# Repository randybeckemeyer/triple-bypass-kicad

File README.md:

# Triple Bypass
The Triple Bypass is an audio/video mod board designed for Sega Genesis/Megadrive consoles. It contains bypass circuitry for RGBs video and also contains a Mega Amp 2.0 audio amplifier designed by Ace and Villahed94.

http://www.sega-16.com/forum/showthread.php?31989-Take-your-Genesis-audio-to-the-next-level-The-Mega-Amp-2-0-is-here!

The schematic circuits are the same as db-electronics version 0.3. The schematic and layout are redrawn with as many built-in library parts as possible. The schematic is shuffled around but contains equivelant circuits with jumpers added. The board is larger than db-electronics version 0.3 and is untested.

# Install Instructions
Use the Mega Amp 2.0 thread for wire tap points on various console revisions.

# Uses Solder Jumpers instead of different Bill of Materials
This is intended to be built with a pick and place assemble line. No need for resistor kits or boards with different build options. The board is designed to be fully populated with one BOM. There are solder jumpers for attenuation resistors and to choose which sound chip your system contains.
* YM2612
* ASIC YM3438
* GOAC YM3438

# PCB Finish
There are no special requirements for the finish of this PCB - a 1.6mm PCB with HASL finish is perfectly acceptable for this PCB.

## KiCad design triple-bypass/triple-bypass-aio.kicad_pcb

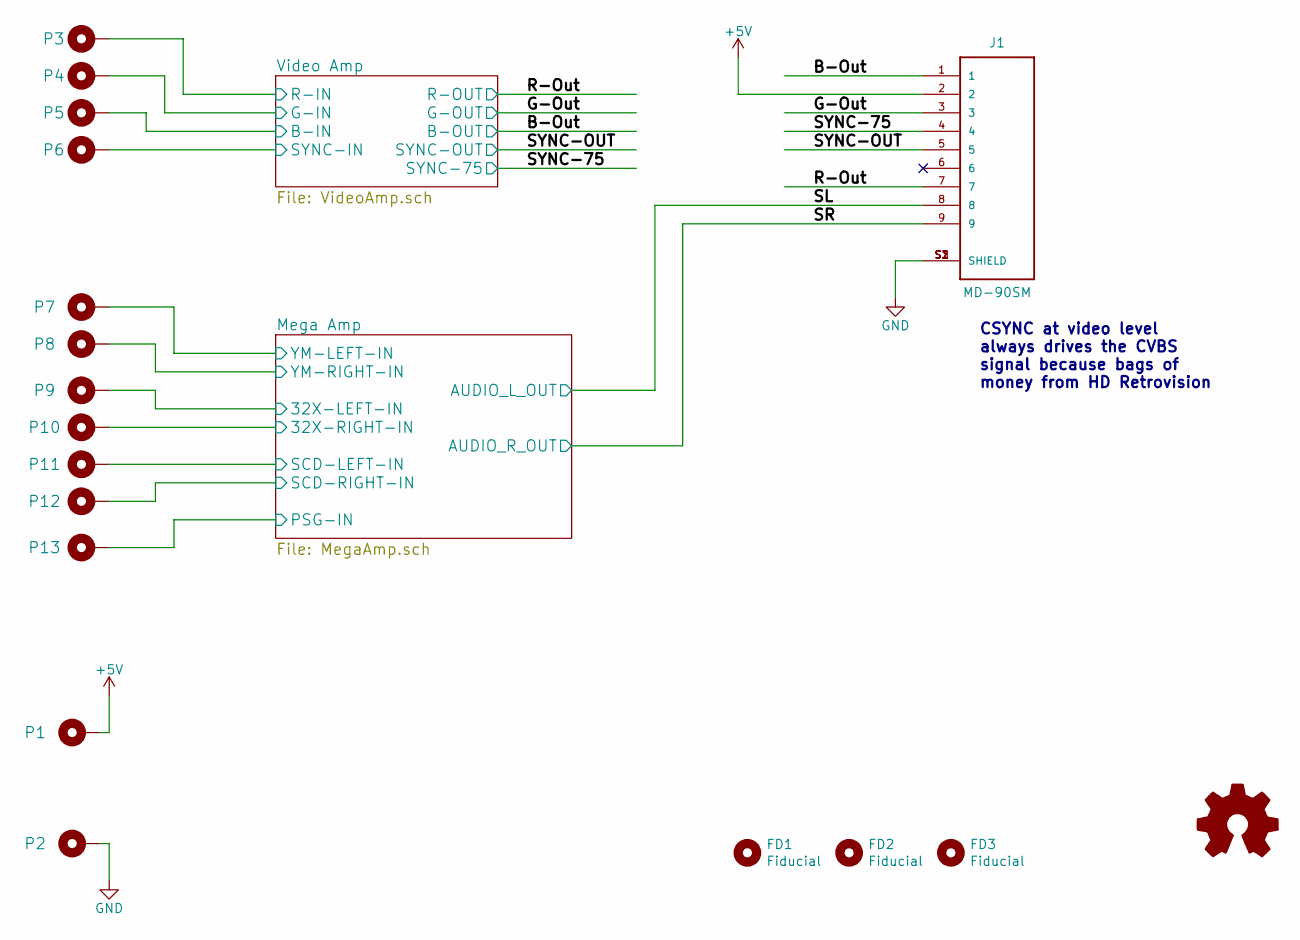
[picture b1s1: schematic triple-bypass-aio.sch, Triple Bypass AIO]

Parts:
FD1, FD2, FD3: Fiducial; Fiducial_0.5mm_Dia_1mm_Outer
J1: MD-90SM; CUI_MD-90SM; Digikey CP-2290-ND
LOGO1: Logo_Open_Hardware_Small; OSHW-Logo2_7.3x6mm_SilkScreen
P1, P2, P3, P4, P5, P6, P7, P8, P9, P10, P11, P12, P13: TP_50; TestPoint_Pad_1.5x1.5mm; Digikey #ND

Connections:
+5V: J1.2, P1.1; also elsewhere on the board
/B-Out: J1.1; also elsewhere on the board
/G-Out: J1.3; also elsewhere on the board
/Mega Amp/32X-LEFT-IN: P9.1; also elsewhere on the board
/Mega Amp/32X-RIGHT-IN: P10.1; also elsewhere on the board
/Mega Amp/PSG-IN: P13.1; also elsewhere on the board
/Mega Amp/SCD-LEFT-IN: P11.1; also elsewhere on the board
/Mega Amp/SCD-RIGHT-IN: P12.1; also elsewhere on the board
/Mega Amp/YM-LEFT-IN: P7.1; also elsewhere on the board
/Mega Amp/YM-RIGHT-IN: P8.1; also elsewhere on the board
/R-Out: J1.7; also elsewhere on the board
/SL: J1.8; also elsewhere on the board
/SR: J1.9; also elsewhere on the board
/SYNC-75: J1.4; also elsewhere on the board
/SYNC-OUT: J1.5; also elsewhere on the board
/Video Amp/B-IN: P5.1; also elsewhere on the board
/Video Amp/G-IN: P4.1; also elsewhere on the board
/Video Amp/R-IN: P3.1; also elsewhere on the board
/Video Amp/SYNC-IN: P6.1; also elsewhere on the board
GND: J1.S1 (SHIELD), J1.S2 (SHIELD), J1.S3 (SHIELD), P2.1; also elsewhere on the board

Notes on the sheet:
CSYNC at video level always drives the CVBS signal because bags of money from HD Retrovision

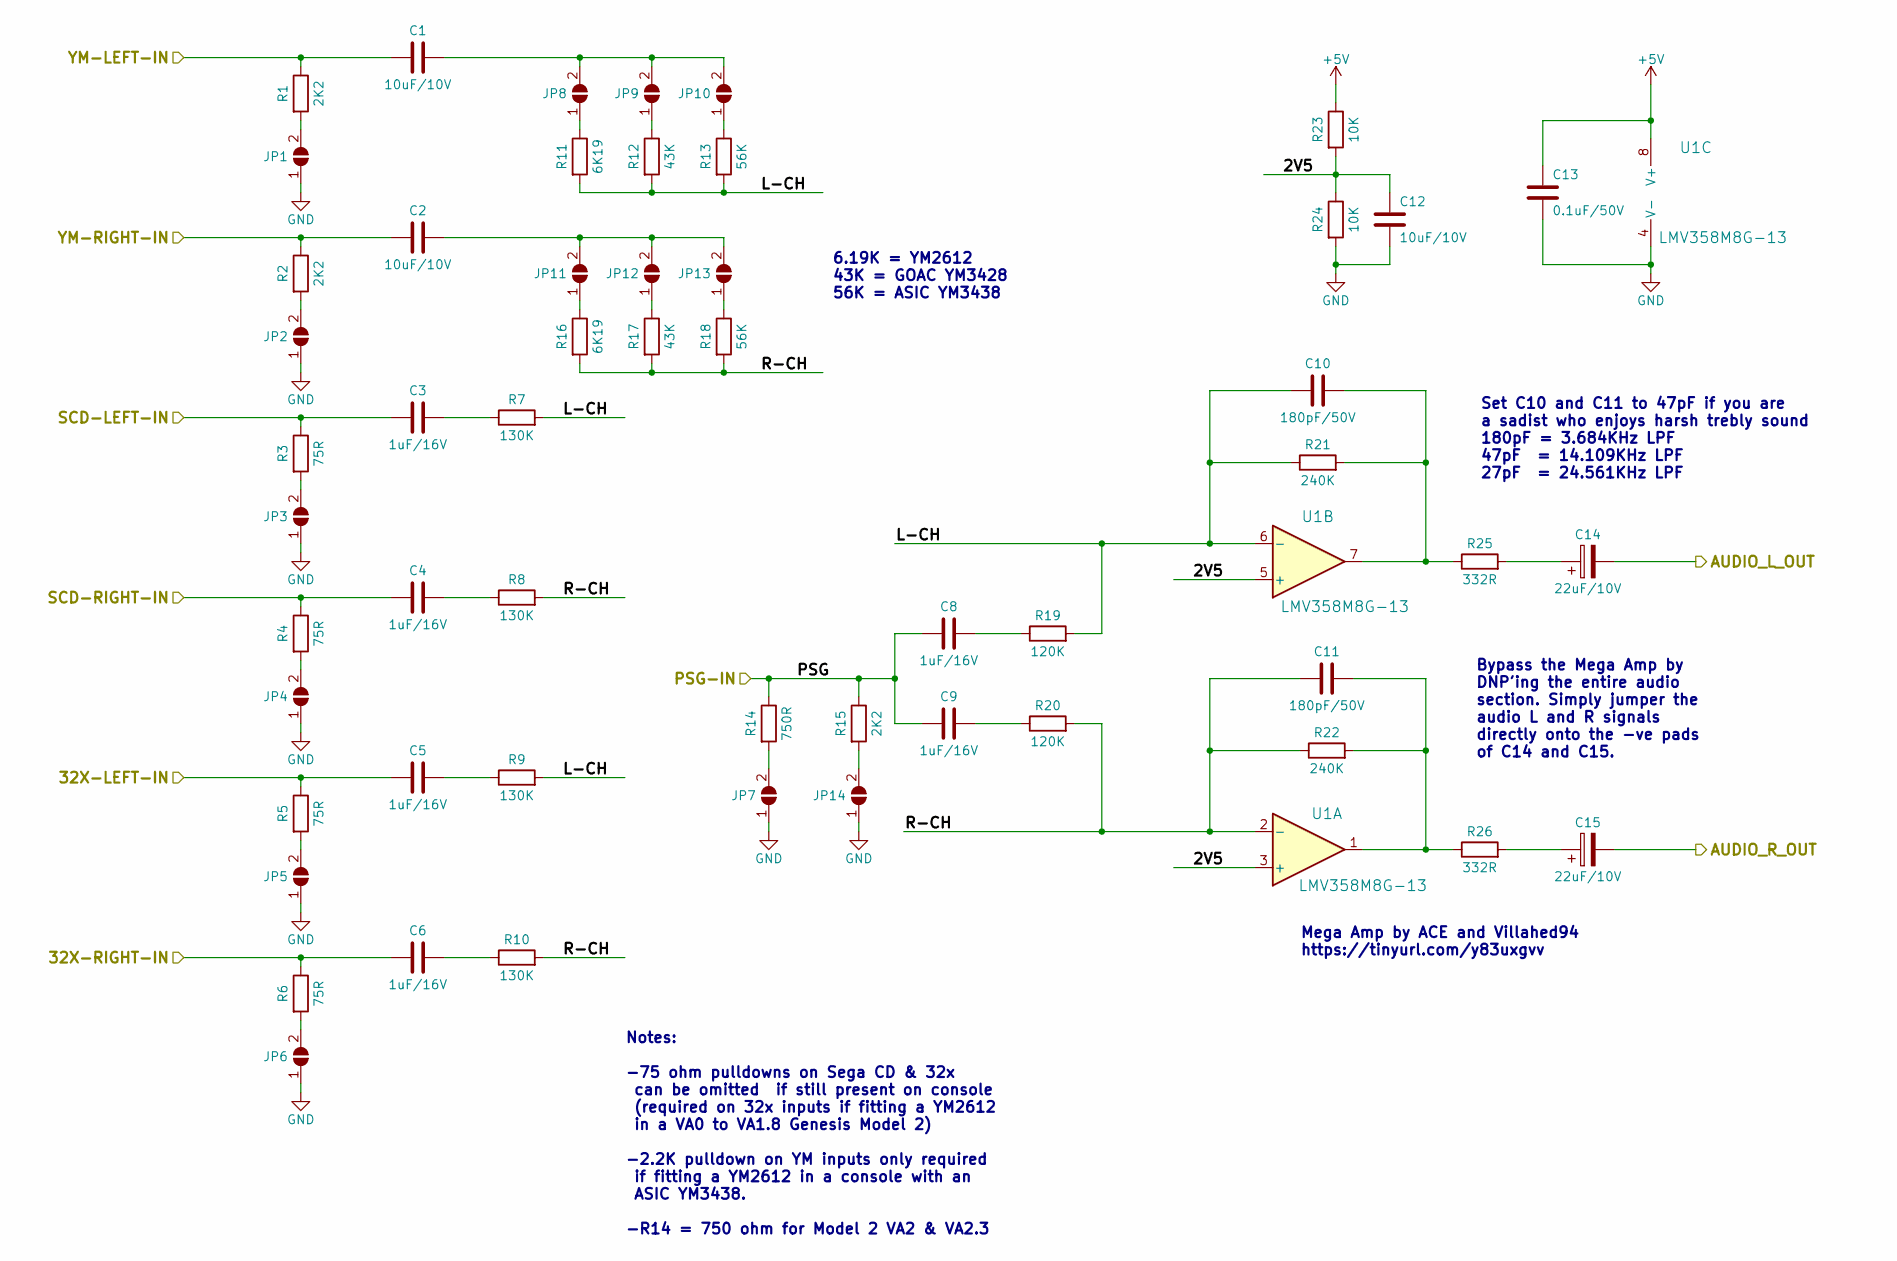
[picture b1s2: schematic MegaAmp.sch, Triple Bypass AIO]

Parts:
C1, C2, C12: 10uF/10V; C_0603_1608Metric; Digikey 478-10766-1-ND
C3, C4, C5, C6, C8, C9: 1uF/16V; C_0603_1608Metric; Digikey 445-1416-1-ND
C10, C11: 180pF/50V; C_0603_1608Metric; Digikey 311-4096-6-ND
C13: 0.1uF/50V; C_0603_1608Metric; Digikey 445-5666-1-ND
C14, C15: 22uF/10V; CP_EIA-3216-18_Kemet-A_Pad1.58x1.35mm_HandSolder; Digikey 478-1663-1-ND
JP1, JP2, JP3, JP4, JP5, JP6, JP7, JP8, JP9, JP10, JP11, JP12, JP13, JP14: SolderJumper_3_Open; SolderJumper-2_P1.3mm_Open_RoundedPad1.0x1.5mm
R1, R2, R15: 2K2; R_0603_1608Metric; Digikey P2.20KHCT-ND
R3, R4, R5, R6: 75R; R_0603_1608Metric; Digikey P75.0HCT-ND
R7, R8, R9, R10: 130K; R_0603_1608Metric; Digikey P130KHCT-ND
R11, R16: 6K19; R_0603_1608Metric; Digikey P6.19KHCT-ND
R12, R17: 43K; R_0603_1608Metric; Digikey P43.0KHCT-ND
R13, R18: 56K; R_0603_1608Metric; Digikey P56.0KHCT-ND
R14: 750R; R_0603_1608Metric; Digikey P750HCT-ND
R19, R20: 120K; R_0603_1608Metric; Digikey P120KHCT-ND
R21, R22: 240K; R_0603_1608Metric; Digikey P240KHCT-ND
R23, R24: 10K; R_0603_1608Metric; Digikey P10.0KHCT-ND
R25, R26: 332R; R_0603_1608Metric; Digikey P332HCT-ND
U1: LMV358M8G-13; TSSOP-8_3x3mm_P0.65mm; Digikey LMV358M8G-13DITR-ND

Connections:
+5V: C13.1, R23.1, U1.8 (V+); also elsewhere on the board
/Mega Amp/2V5: C12.2, R23.2, R24.1, U1.3 (+), U1.5 (+)
/Mega Amp/32X-LEFT-IN: C5.1, R5.1; also elsewhere on the board
/Mega Amp/32X-RIGHT-IN: C6.1, R6.1; also elsewhere on the board
/Mega Amp/L-CH: C10.1, R7.2, R9.2, R11.2, R12.2, R13.2, R19.2, R21.1, U1.6 (-)
/Mega Amp/PSG-IN: C8.1, C9.1, R14.1, R15.1; also elsewhere on the board
/Mega Amp/R-CH: C11.1, R8.2, R10.2, R16.2, R17.2, R18.2, R20.2, R22.1, U1.2 (-)
/Mega Amp/SCD-LEFT-IN: C3.1, R3.1; also elsewhere on the board
/Mega Amp/SCD-RIGHT-IN: C4.1, R4.1; also elsewhere on the board
/Mega Amp/YM-LEFT-IN: C1.2, R1.1; also elsewhere on the board
/Mega Amp/YM-RIGHT-IN: C2.2, R2.1; also elsewhere on the board
/SL: C14.2; also elsewhere on the board
/SR: C15.2; also elsewhere on the board
GND: C12.1, C13.2, JP1.1 (A), JP2.1 (A), JP3.1 (A), JP4.1 (A), JP5.1 (A), JP6.1 (A), JP7.1 (A), JP14.1 (A), R24.2, U1.4 (V-); also elsewhere on the board
unnamed: C1.1, JP8.2 (B), JP9.2 (B), JP10.2 (B)
unnamed: C2.1, JP11.2 (B), JP12.2 (B), JP13.2 (B)
unnamed: C3.2, R7.1
unnamed: C4.2, R8.1
unnamed: C5.2, R9.1
unnamed: C6.2, R10.1
unnamed: C8.2, R19.1
unnamed: C9.2, R20.1
unnamed: C10.2, R21.2, R25.1, U1.7
unnamed: C11.2, R22.2, R26.1, U1.1
unnamed: C14.1, R25.2
unnamed: C15.1, R26.2
unnamed: JP1.2 (B), R1.2
unnamed: JP2.2 (B), R2.2
unnamed: JP3.2 (B), R3.2
unnamed: JP4.2 (B), R4.2
unnamed: JP5.2 (B), R5.2
unnamed: JP6.2 (B), R6.2
unnamed: JP7.2 (B), R14.2
unnamed: JP8.1 (A), R11.1
unnamed: JP9.1 (A), R12.1
unnamed: JP10.1 (A), R13.1
unnamed: JP11.1 (A), R16.1
unnamed: JP12.1 (A), R17.1
unnamed: JP13.1 (A), R18.1
unnamed: JP14.2 (B), R15.2

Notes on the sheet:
Mega Amp by ACE and Villahed94 https://tinyurl.com/y83uxgvv
Set C10 and C11 to 47pF if you are a sadist who enjoys harsh trebly sound 180pF = 3.684KHz LPF 47pF = 14.109KHz LPF 27pF = 24.561KHz LPF
Bypass the Mega Amp by DNP'ing the entire audio section. Simply jumper the audio L and R signals directly onto the -ve pads of C14 and C15.
Notes: -75 ohm pulldowns on Sega CD & 32x can be omitted if still present on console (required on 32x inputs if fitting a YM2612 in a VA0 to VA1.8 Genesis Model 2) -2.2K pulldown on YM inputs only required if fitting a YM2612 in a console with an ASIC YM3438. -R14 = 750 ohm for Model 2 VA2 & VA2.3
6.19K = YM2612 43K = GOAC YM3428 56K = ASIC YM3438

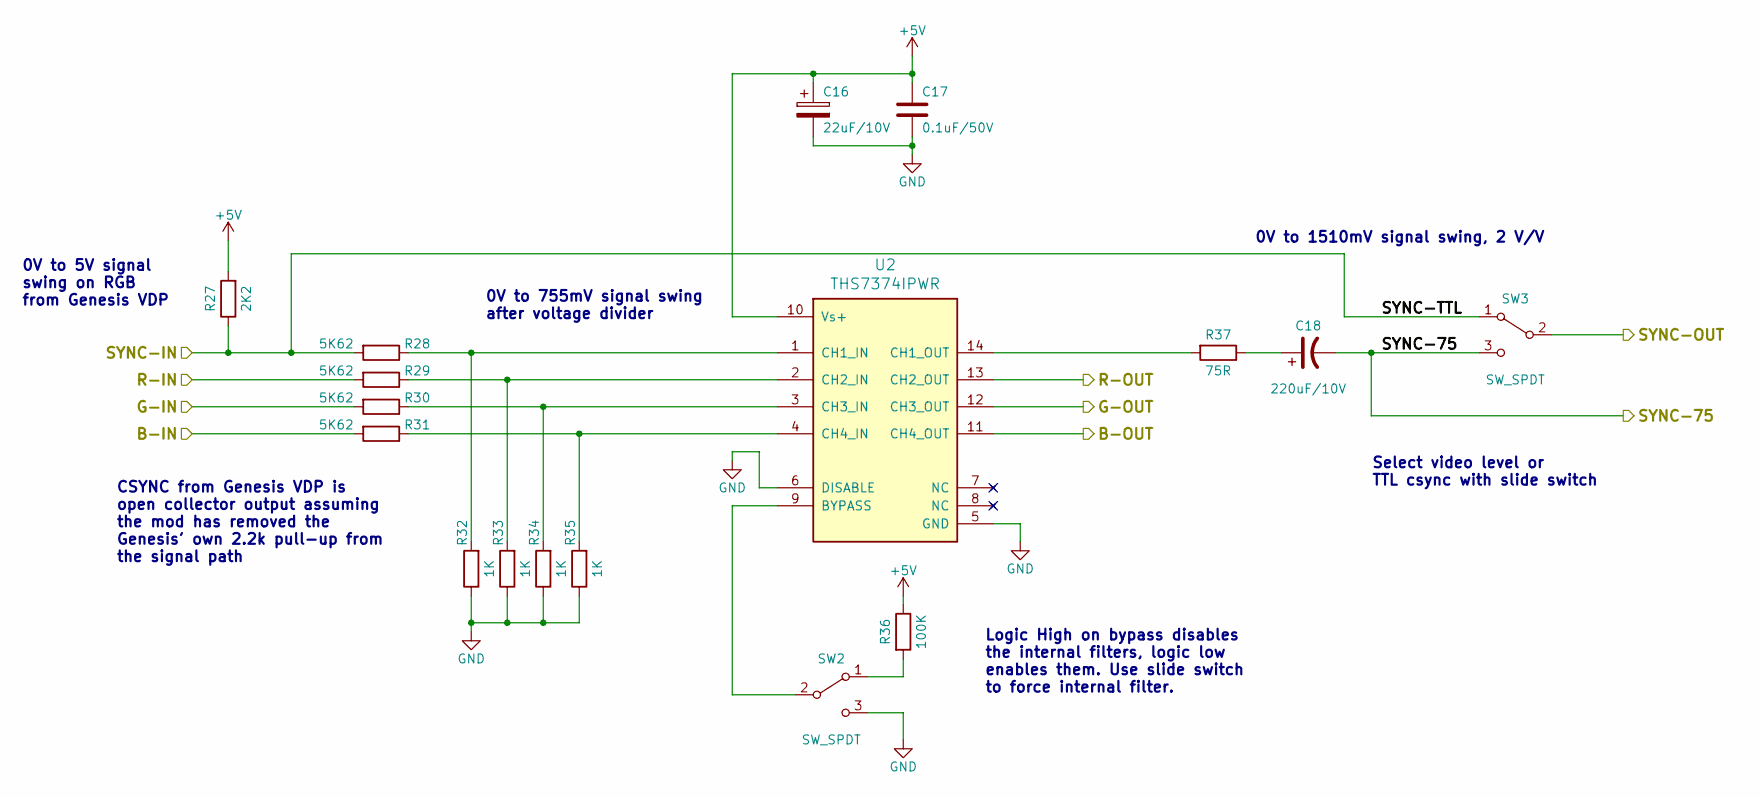
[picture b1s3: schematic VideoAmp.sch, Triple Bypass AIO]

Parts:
C16: 22uF/10V; CP_EIA-3216-18_Kemet-A_Pad1.58x1.35mm_HandSolder; Digikey 478-1663-1-ND
C17: 0.1uF/50V; C_0603_1608Metric; Digikey 445-5666-1-ND
C18: 220uF/10V; CP_Elec_6.3x5.4_Nichicon; Digikey 493-6210-1-ND
R27: 2K2; R_0603_1608Metric; Digikey P2.20KHCT-ND
R28, R29, R30, R31: 5K62; R_0603_1608Metric; Digikey P5.62KHCT-ND
R32, R33, R34, R35: 1K; R_0603_1608Metric; Digikey P1.00KHCT-ND
R36: 100K; R_0603_1608Metric; Digikey RHM100KAYCT-ND
R37: 75R; R_0603_1608Metric; Digikey P75.0HCT-ND
SW2, SW3: SW_SPDT; CL-SB-12B-01; Digikey 563-1318-1-ND
U2: THS7374IPWR; TSSOP-14_4.4x5mm_P0.65mm; Digikey 296-41661-1-ND

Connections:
+5V: C16.1, C17.1, R27.2, R36.1, U2.10 (Vs+); also elsewhere on the board
/B-Out: U2.11 (CH4_OUT); also elsewhere on the board
/G-Out: U2.12 (CH3_OUT); also elsewhere on the board
/R-Out: U2.13 (CH2_OUT); also elsewhere on the board
/SYNC-75: C18.2, SW3.3 (C); also elsewhere on the board
/SYNC-OUT: SW3.2 (B); also elsewhere on the board
/Video Amp/B-IN: R31.2; also elsewhere on the board
/Video Amp/G-IN: R30.2; also elsewhere on the board
/Video Amp/R-IN: R29.2; also elsewhere on the board
/Video Amp/SYNC-IN: R27.1, R28.2, SW3.1 (A); also elsewhere on the board
GND: C16.2, C17.2, R32.1, R33.1, R34.1, R35.1, SW2.3 (C), U2.5 (GND), U2.6 (DISABLE); also elsewhere on the board
unnamed: C18.1, R37.1
unnamed: R28.1, R32.2, U2.1 (CH1_IN)
unnamed: R29.1, R33.2, U2.2 (CH2_IN)
unnamed: R30.1, R34.2, U2.3 (CH3_IN)
unnamed: R31.1, R35.2, U2.4 (CH4_IN)
unnamed: R36.2, SW2.1 (A)
unnamed: R37.2, U2.14 (CH1_OUT)
unnamed: SW2.2 (B), U2.9 (BYPASS)

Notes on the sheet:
Logic High on bypass disables the internal filters, logic low enables them. Use slide switch to force internal filter.
Select video level or TTL csync with slide switch
0V to 5V signal swing on RGB from Genesis VDP
0V to 755mV signal swing after voltage divider
CSYNC from Genesis VDP is open collector output assuming the mod has removed the Genesis' own 2.2k pull-up from the signal path
0V to 1510mV signal swing, 2 V/V

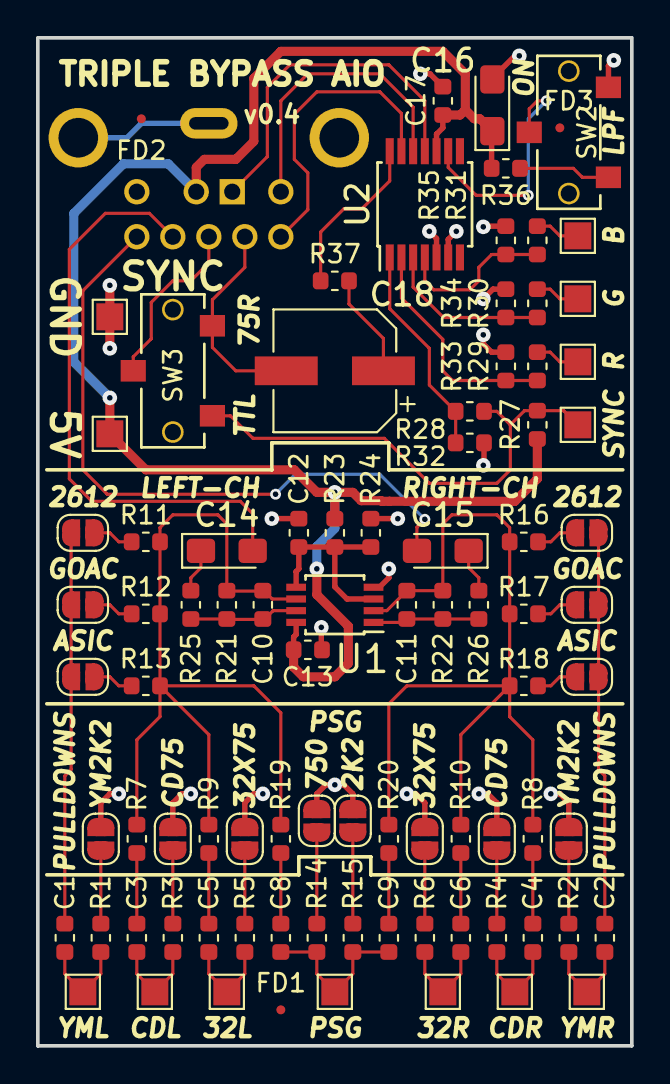
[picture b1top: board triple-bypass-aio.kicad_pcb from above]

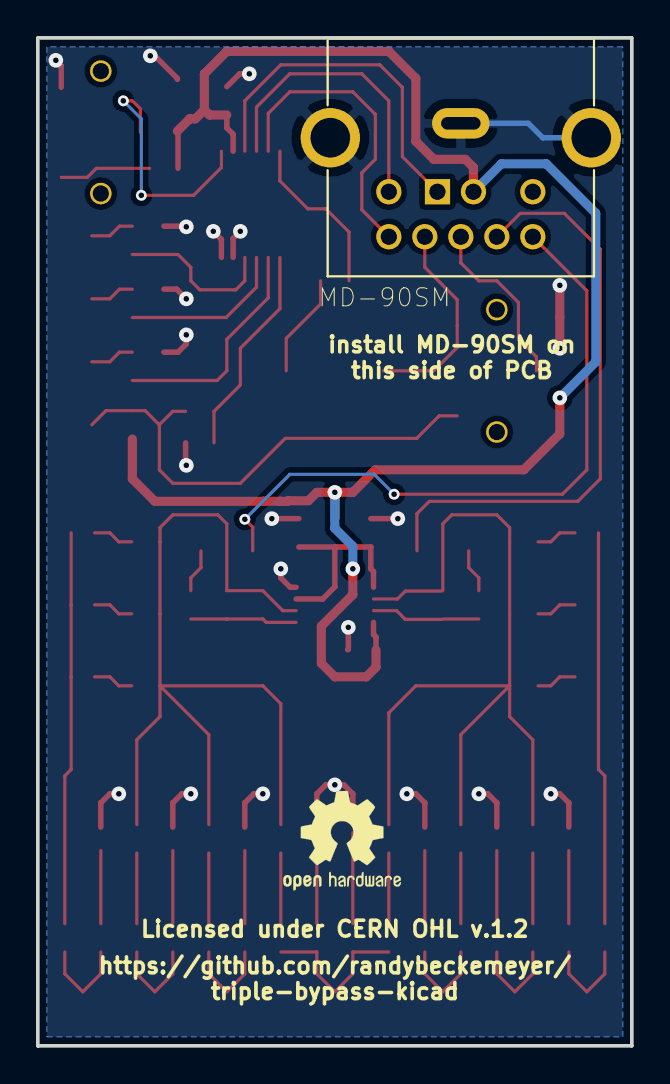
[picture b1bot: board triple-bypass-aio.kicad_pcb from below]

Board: 2 copper layers, 33.0 x 56.0 mm, 90 parts (2 on the bottom side), 57 nets.

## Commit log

2018-12-16 Organize and export pdf
2018-12-17 Increase 5V rail width
2019-03-23 Rename to AIO
    Moved offset of PCB so footprints are on grid. Saved in KiCad version 5.1.0. Export gerbers. Found and deleted board cuts in MiniDIN footprint.

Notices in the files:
triple-bypass/MegaAmp.sch:
Licensed under CERN OHL v.1.2
